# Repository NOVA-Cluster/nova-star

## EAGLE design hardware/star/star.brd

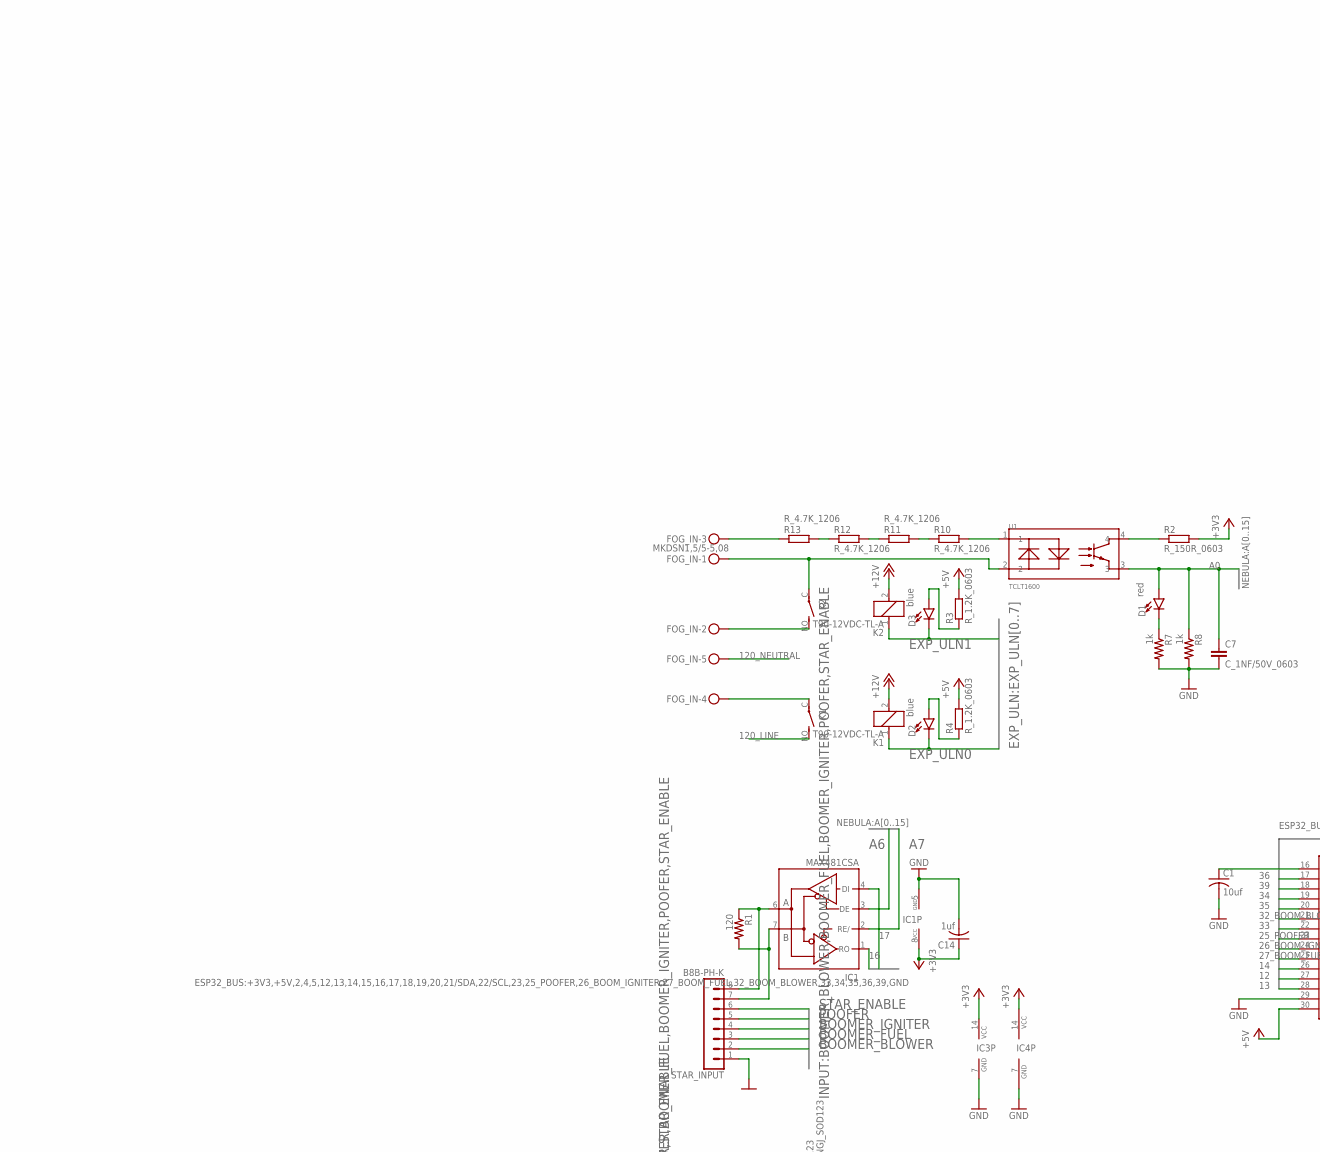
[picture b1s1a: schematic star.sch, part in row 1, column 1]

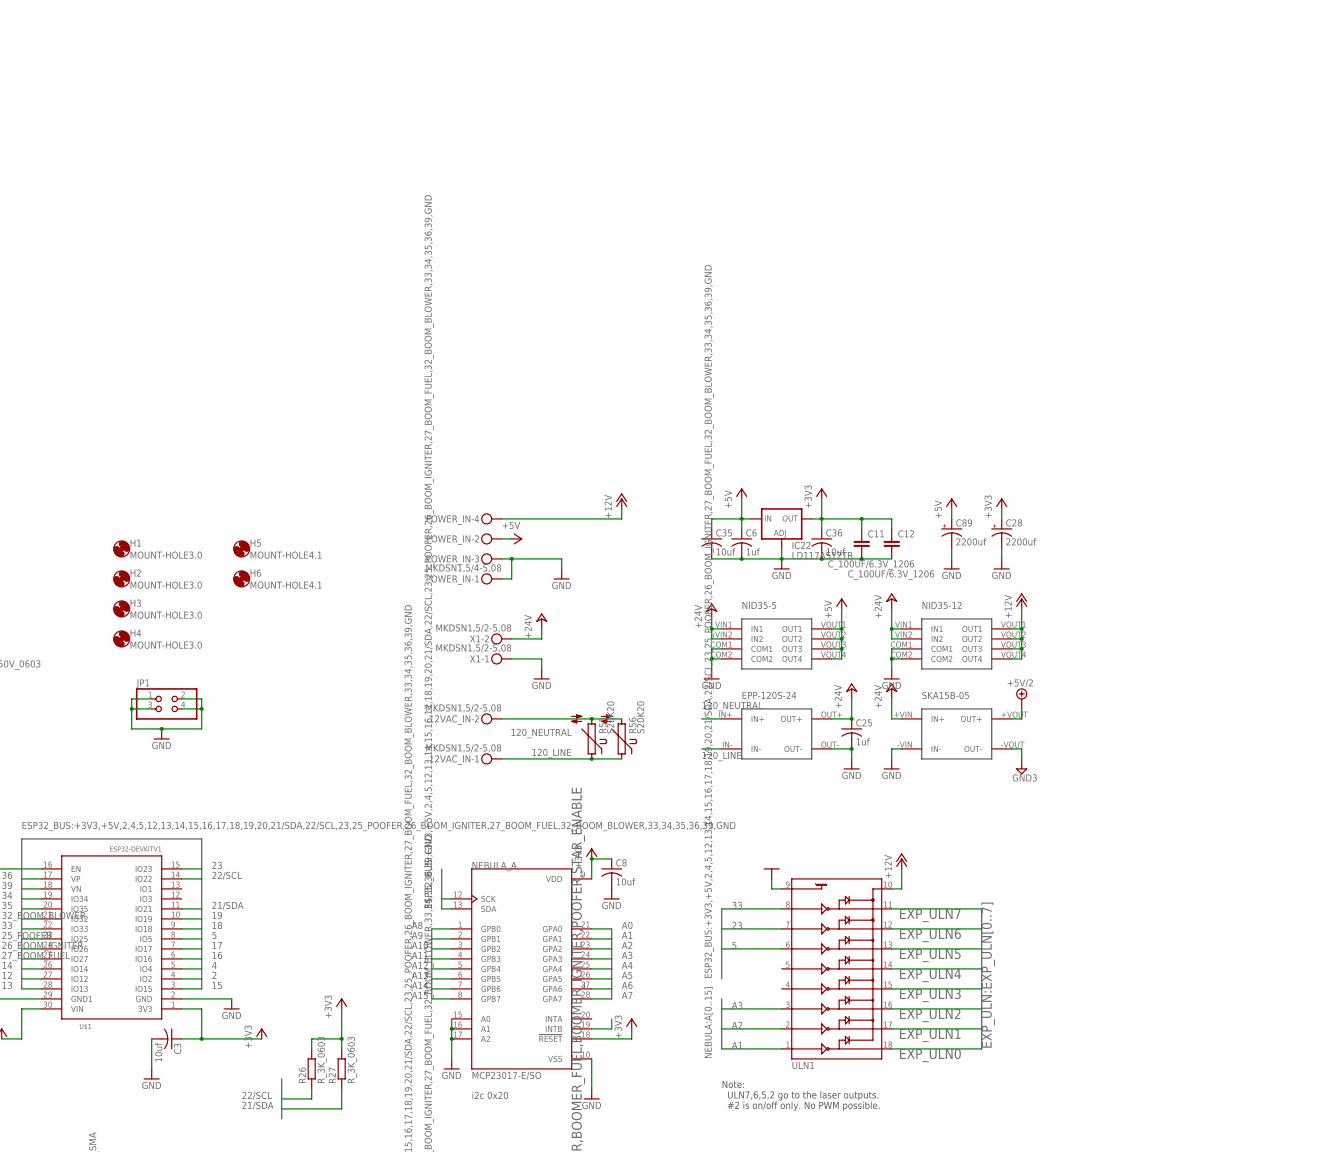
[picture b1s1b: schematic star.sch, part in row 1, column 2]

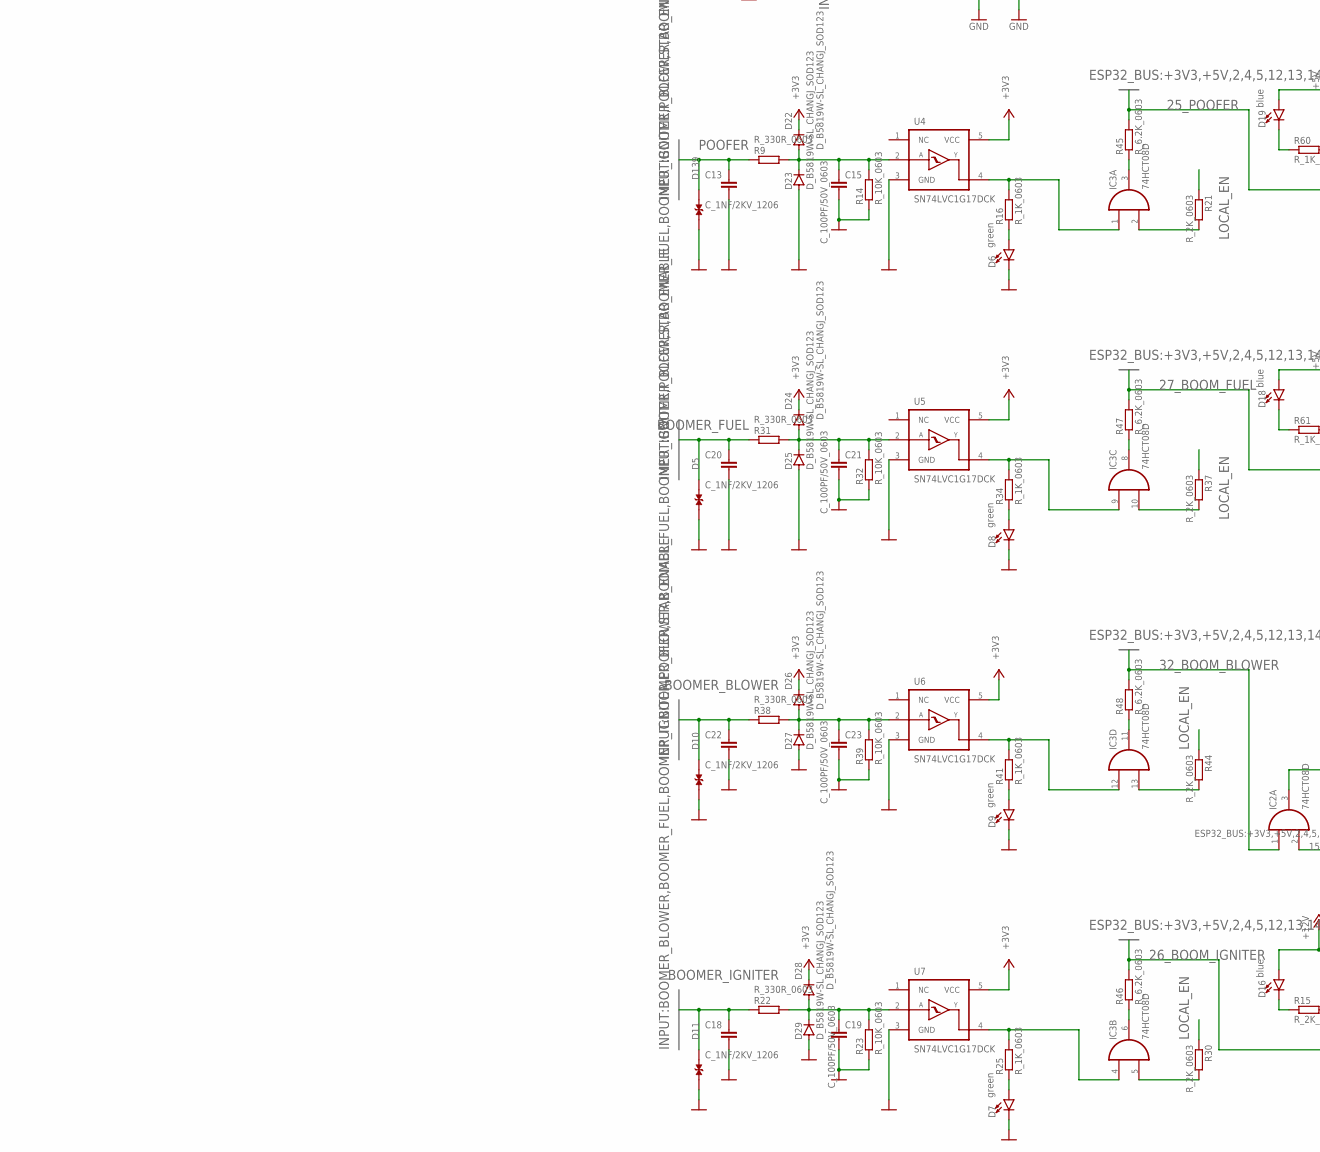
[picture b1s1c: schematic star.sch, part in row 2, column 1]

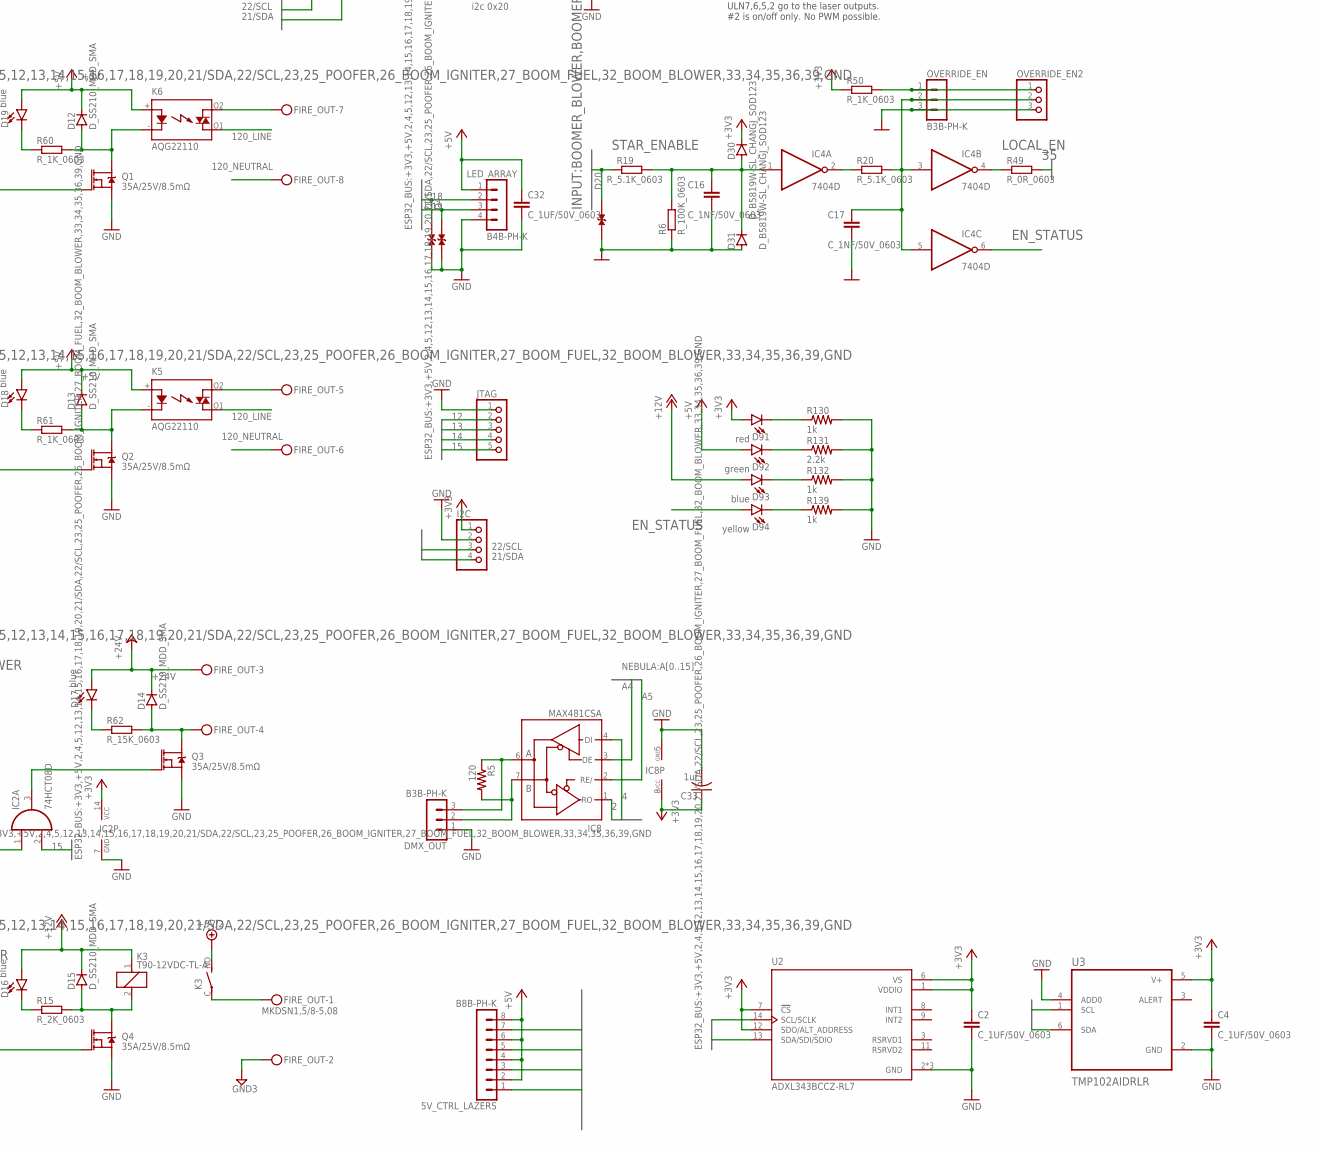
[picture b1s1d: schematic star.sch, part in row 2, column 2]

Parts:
5V_CTRL_LAZERS: B8B-PH-K
12VAC_IN: MKDSN1,5/2-5,08
C1, C3, C8, C35, C36: 10uf; C0603; LCSC_PART C19702
C2, C4, C32: C_1UF/50V_0603; C0603
C6, C14, C25, C33: 1uf; C0805; LCSC_PART C15849
C7, C16, C17: C_1NF/50V_0603; C0603
C11, C12: C_100UF/6.3V_1206; C1206
C13, C18, C20, C22: C_1NF/2KV_1206; C1206
C15, C19, C21, C23: C_100PF/50V_0603; C0603
C28, C89: 2200uf; E5-13
D1, D91: red; LED-0603; JLC_ROTATION 180
D2, D3, D16, D17, D18, D19, D93: blue; LED-0603; JLC_ROTATION 180
D4, D5, D10, D11, D20, D21, D139: SMBJ8.0CA; DIOM4336X265N; LCSC_PART C78757
D6, D7, D8, D9, D92: green; LED-0603; JLC_ROTATION 180
D12, D13, D14, D15: D_SS210_MDD_SMA; DO-214AC
D22, D23, D24, D25, D26, D27, D28, D29, D30, D31: D_B5819W-SL_CHANGJ_SOD123; SOD123
D94: yellow; LED-0603; JLC_ROTATION 180
DMX_OUT: B3B-PH-K
EPP-120S-24: EPP-120S; EPS-25
FIRE_OUT: MKDSN1,5/8-5,08
FOG_IN: MKDSN1,5/5-5,08
H1, H2, H3, H4: MOUNT-HOLE3.0; 3,0
H5, H6: MOUNT-HOLE4.1; 4,1
I2C: PINHD-1X4; 1X04
IC1, IC8: MAX481CSA; SO08; LCSC_PART C8963
IC2, IC3: 74HCT08D; SO14; LCSC_PART C5593
IC4: 7404D; SO14; LCSC_PART C5590
IC22: LD117AS12TR; SOT223; LCSC_PART C347222
JP1: PINHD-2X2; 2X02
JTAG: PINHD-1X5; 1X05
K1, K2, K3: T90-12VDC-TL-A; JT1A-PCB
K5, K6: AQG22110; AQG
LED_ARRAY: B4B-PH-K
NEBULA_A: MCP23017-E/SO; SOIC127P1030X265-28N; LCSC_PART C629440
NID35-5, NID35-12: NID35
OVERRIDE_EN: B3B-PH-K
OVERRIDE_EN2: PINHD-1X3; 1X03
POWER_IN: MKDSN1,5/4-5,08
Q1, Q2, Q3, Q4: 35A/25V/8.5mΩ; DPAK; LCSC_PART C2995335
R1, R5: 120; R0603; LCSC_PART C22787
R2: R_150R_0603; R0603
R3, R4: R_1.2K_0603; R0603
R6: R_100K_0603; R0603
R7, R8, R130, R132, R139: 1k; R0603; LCSC_PART C21190
R9, R22, R31, R38: R_330R_0603; R0603
R10, R11, R12, R13: R_4.7K_1206; R1206
R14, R23, R32, R39: R_10K_0603; R0603
R15, R21, R30, R37, R44: R_2K_0603; R0603
R16, R25, R34, R41, R50, R60, R61: R_1K_0603; R0603
R19, R20: R_5.1K_0603; R0603
R26, R27: R_3K_0603; R0603
R45, R46, R47, R48: R_6.2K_0603; R0603
R49: R_0R_0603; R0603
R55, R56: S20K20
R62: R_15K_0603; R0603
R131: 2.2k; R0603; LCSC_PART C4190
SKA15B-05: SKA15B
STAR_INPUT: B8B-PH-K
U1: TCLT1600; SOP254P1015X230-4N; LCSC_PART C553998
U2: ADXL343BCCZ-RL7; PQFN80P300X500X100-14N; LCSC_PART C9667
U3: TMP102AIDRLR; SOT50P160X60-6N
U4, U5, U6, U7: SN74LVC1G17DCK; SC70-5
U$1: ESP32DEVKITV1; ESP32-DEVKITV1
ULN1: ULN2803SOICW; SO18L; LCSC_PART C9683
X1: MKDSN1,5/2-5,08

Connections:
2: IC8.1 (RO), U$1.4 (IO2)
4: IC8.4 (DI), U$1.5 (IO4)
5: U$1.8 (IO5), ULN1.6
12: JTAG.2, U$1.27 (IO12)
13: JTAG.3, U$1.28 (IO13)
14: JTAG.4, U$1.26 (IO14)
15: IC2.2 (I1), JTAG.5, U$1.3 (IO15)
16: IC1.1 (RO), U$1.6 (IO16)
17: IC1.4 (DI), U$1.7 (IO17)
18: D21.2, LED_ARRAY.2, U$1.9 (IO18)
19: D4.2, LED_ARRAY.3, U$1.10 (IO19)
21/SDA: I2C.4, NEBULA_A.13 (SDA), R27.1, U2.13 (SDA/SDI/SDIO), U3.6 (SDA), U$1.11 (IO21)
22/SCL: I2C.3, NEBULA_A.12 (SCK), R26.1, U2.14 (SCL/SCLK), U3.1 (SCL), U$1.14 (IO22)
23: U$1.15 (IO23), ULN1.7
25_POOFER: Q1.1 (G), R45.2, U$1.23 (IO25)
26_BOOM_IGNITER: Q4.1 (G), R46.2, U$1.24 (IO26)
27_BOOM_FUEL: Q2.1 (G), R47.2, U$1.25 (IO27)
32_BOOM_BLOWER: IC2.1 (I0), R48.2, U$1.21 (IO32)
33: U$1.22 (IO33), ULN1.8
34: NEBULA_A.19 (INTB), U$1.19 (IO34)
35: R49.2, U$1.20 (IO35)
36: U$1.17 (VP)
39: U$1.18 (VN)
120_LINE: 12VAC_IN.1, EPP-120S-24.IN-, K1.NO (S), K5.O1 (DS2), K6.O1 (DS2), R55.1, R56.1
120_NEUTRAL: 12VAC_IN.2, EPP-120S-24.IN+, FIRE_OUT.6, FIRE_OUT.8, FOG_IN.5, R55.2, R56.2
+3V3: C2.1, C3.1, C4.1, C8.1, C11.1, C12.1, C14.1, C28.+, C33.1, C36.1, D22.C, D24.C, D26.C, D28.C, D30.C, D91.A, I2C.1, IC1.8 (VCC), IC2.14 (VCC), IC3.14 (VCC), IC4.14 (VCC), IC8.8 (VCC), IC22.4 (OUT), NEBULA_A.9 (VDD), NEBULA_A.18 (!RESET), R2.2, R26.2, R27.2, R50.1, U2.1 (VDDIO), U2.6 (VS), U2.7 (!CS), U2.12 (SDO/ALT_ADDRESS), U3.5 (V+), U4.5 (VCC), U5.5 (VCC), U6.5 (VCC), U7.5 (VCC), U$1.1 (3V3)
+5V: 5V_CTRL_LAZERS.2, 5V_CTRL_LAZERS.4, 5V_CTRL_LAZERS.6, 5V_CTRL_LAZERS.8, C6.1, C32.1, C35.1, C89.+, D12.C, D13.C, D18.A, D19.A, D92.A, IC22.3 (IN), K5.+ (A), K6.+ (A), LED_ARRAY.1, NID35-5.VOUT1 (OUT1), NID35-5.VOUT2 (OUT2), NID35-5.VOUT3 (OUT3), NID35-5.VOUT4 (OUT4), POWER_IN.2, R3.2, R4.2, U$1.30 (VIN)
+5V/2: K3.NO (S), SKA15B-05.+VOUT (OUT+)
+12V: D15.C, D16.A, D93.A, K1.2, K2.2, K3.1, NID35-12.VOUT1 (OUT1), NID35-12.VOUT2 (OUT2), NID35-12.VOUT3 (OUT3), NID35-12.VOUT4 (OUT4), POWER_IN.4, ULN1.10
+24V: C25.1, D14.C, D17.A, EPP-120S-24.OUT+, FIRE_OUT.3, NID35-5.VIN1 (IN1), NID35-5.VIN2 (IN2), NID35-12.VIN1 (IN1), NID35-12.VIN2 (IN2), SKA15B-05.+VIN (IN+), X1.2
A0: C7.1, D1.A, NEBULA_A.21 (GPA0), R8.1, U1.3
A1: NEBULA_A.22 (GPA1), ULN1.1
A2: NEBULA_A.23 (GPA2), ULN1.2
A3: NEBULA_A.24 (GPA3), ULN1.3
A4: IC8.3 (DE), NEBULA_A.25 (GPA4)
A5: IC8.2 (RE/), NEBULA_A.26 (GPA5)
A6: IC1.3 (DE), NEBULA_A.27 (GPA6)
A7: IC1.2 (RE/), NEBULA_A.28 (GPA7)
A8: NEBULA_A.1 (GPB0)
A9: NEBULA_A.2 (GPB1)
A10: NEBULA_A.3 (GPB2)
A11: NEBULA_A.4 (GPB3)
A12: NEBULA_A.5 (GPB4)
A13: NEBULA_A.6 (GPB5)
A14: NEBULA_A.7 (GPB6)
A15: NEBULA_A.8 (GPB7)
BOOMER_BLOWER: C22.1, D10.2, R38.1, STAR_INPUT.2
BOOMER_FUEL: C20.1, D5.2, R31.1, STAR_INPUT.3
BOOMER_IGNITER: C18.1, D11.2, R22.1, STAR_INPUT.4
EN_STATUS: D94.A, IC4.6 (O)
EXP_ULN0: D2.C, K1.1, ULN1.18
EXP_ULN1: D3.C, K2.1, ULN1.17
EXP_ULN2: 5V_CTRL_LAZERS.7, ULN1.16
EXP_ULN3: ULN1.15
EXP_ULN4: ULN1.14
EXP_ULN5: 5V_CTRL_LAZERS.5, ULN1.13
EXP_ULN6: 5V_CTRL_LAZERS.3, ULN1.12
EXP_ULN7: 5V_CTRL_LAZERS.1, ULN1.11
GND: C1.2, C2.2, C3.2, C4.2, C6.2, C7.2, C8.2, C11.2, C12.2, C13.2, C14.2, C15.2, C16.2, C17.2, C18.2, C19.2, C20.2, C21.2, C22.2, C23.2, C25.2, C28.-, C32.2, C33.2, C35.2, C36.2, C89.-, D4.1, D5.1, D6.C, D7.C, D8.C, D9.C, D10.1, D11.1, D20.1, D21.1, D23.A, D25.A, D27.A, D29.A, D31.A, D139.1, DMX_OUT.1, EPP-120S-24.OUT-, I2C.2, IC1.5 (GND), IC2.7 (GND), IC3.7 (GND), IC4.7 (GND), IC8.5 (GND), IC22.1 (ADJ), JP1.1, JP1.2, JP1.3, JP1.4, JTAG.1, LED_ARRAY.4, NEBULA_A.10 (VSS), NEBULA_A.15 (A0), NEBULA_A.16 (A1), NEBULA_A.17 (A2), NID35-5.COM1, NID35-5.COM2, NID35-12.COM1, NID35-12.COM2, OVERRIDE_EN.3, OVERRIDE_EN2.3, POWER_IN.1, POWER_IN.3, Q1.3 (S), Q2.3 (S), Q3.3 (S), Q4.3 (S), R6.1, R7.2, R8.2, R14.1, R23.1, R32.1, R39.1, R130.2, R131.2, R132.2, R139.2, SKA15B-05.-VIN (IN-), STAR_INPUT.1, U2.2 (GND), U2.4 (GND), U2.5 (GND), U3.2 (GND), U3.4 (ADD0), U4.3 (GND), U5.3 (GND), U6.3 (GND), U7.3 (GND), U$1.2 (GND), U$1.29 (GND1), ULN1.9, X1.1
GND3: FIRE_OUT.2, SKA15B-05.-VOUT (OUT-)
LOCAL_EN: IC4.4 (O), R21.1, R30.1, R37.1, R44.1, R49.1
unnamed: C1.1, U$1.16 (EN)
unnamed: R2.1, U1.4
unnamed: D2.A, R4.1
unnamed: D3.A, R3.1
unnamed: DMX_OUT.2, IC8.7 (B), R5.2
unnamed: DMX_OUT.3, IC8.6 (A), R5.1
unnamed: FOG_IN.3, R13.1
unnamed: R12.1, R13.2
unnamed: R11.1, R12.2
unnamed: R10.1, R11.2
unnamed: R10.2, U1.1
unnamed: D1.C, R7.1
unnamed: FOG_IN.2, K2.NO (S)
unnamed: FOG_IN.4, K1.C
unnamed: FOG_IN.1, K2.C, U1.2
unnamed: IC3.1 (I0), R16.2, U4.4 (Y)
unnamed: C15.1, D22.A, D23.C, R9.2, R14.2, U4.2 (A)
unnamed: D6.A, R16.1
unnamed: IC4.2 (O), R20.1
unnamed: C17.1, IC4.3 (I), IC4.5 (I), OVERRIDE_EN.2, OVERRIDE_EN2.2, R20.2
unnamed: C16.1, D30.A, D31.C, IC4.1 (I), R6.2, R19.2
unnamed: IC3.2 (I1), R21.2
unnamed: C19.1, D28.A, D29.C, R22.2, R23.2, U7.2 (A)
unnamed: IC3.4 (I0), R25.2, U7.4 (Y)
unnamed: D7.A, R25.1
unnamed: IC3.5 (I1), R30.2
unnamed: C21.1, D24.A, D25.C, R31.2, R32.2, U5.2 (A)
unnamed: IC3.9 (I0), R34.2, U5.4 (Y)
unnamed: D8.A, R34.1
unnamed: IC3.10 (I1), R37.2
unnamed: C23.1, D26.A, D27.C, R38.2, R39.2, U6.2 (A)
unnamed: IC3.12 (I0), R41.2, U6.4 (Y)
unnamed: D9.A, R41.1
unnamed: IC3.13 (I1), R44.2
unnamed: IC3.3 (O), R45.1
unnamed: IC3.6 (O), R46.1
unnamed: IC3.8 (O), R47.1
unnamed: IC3.11 (O), R48.1
unnamed: D13.A, K5.- (K), Q2.4 (D), R61.2
unnamed: FIRE_OUT.7, K6.O2 (DS1)
unnamed: D12.A, K6.- (K), Q1.4 (D), R60.2
unnamed: FIRE_OUT.5, K5.O2 (DS1)
unnamed: D14.A, FIRE_OUT.4, Q3.4 (D), R62.2
unnamed: D15.A, K3.2, Q4.4 (D), R15.2
unnamed: FIRE_OUT.1, K3.C
unnamed: D16.C, R15.1
unnamed: D17.C, R62.1
unnamed: D18.C, R61.1
unnamed: D19.C, R60.1
unnamed: OVERRIDE_EN.1, OVERRIDE_EN2.1, R50.2
unnamed: IC2.3 (O), Q3.1 (G)
unnamed: IC1.7 (B), R1.2, STAR_INPUT.7
unnamed: IC1.6 (A), R1.1, STAR_INPUT.8
unnamed: D91.C, R130.1
unnamed: D92.C, R131.1
unnamed: D93.C, R132.1
unnamed: D94.C, R139.1
POOFER: C13.1, D139.2, R9.1, STAR_INPUT.5
STAR_ENABLE: D20.2, R19.1, STAR_INPUT.6

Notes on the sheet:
i2c 0x20
Note: ULN7,6,5,2 go to the laser outputs. #2 is on/off only. No PWM possible.

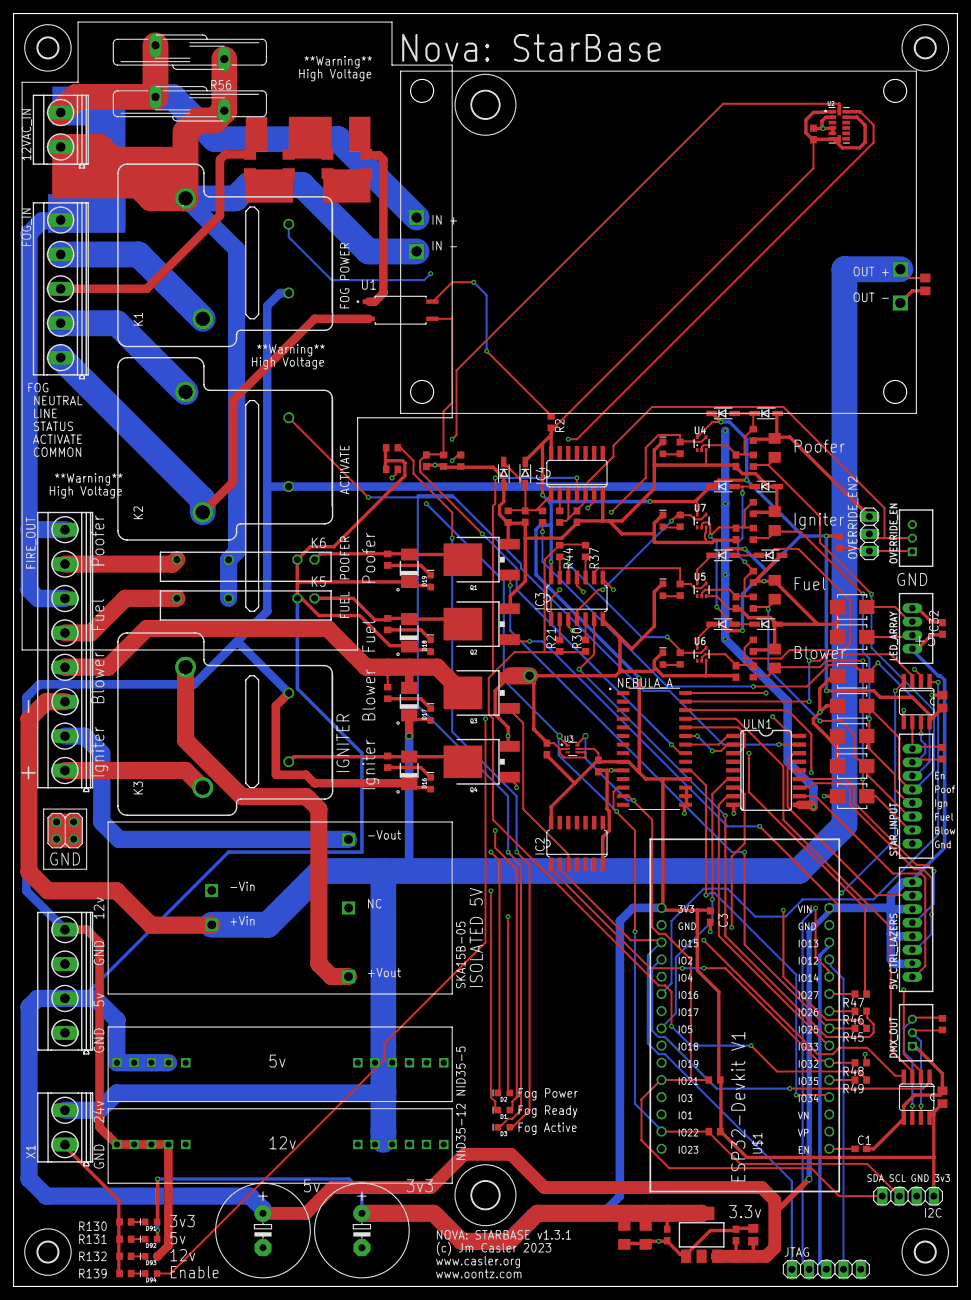
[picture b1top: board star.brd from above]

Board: 4 copper layers, 139.4 x 187.9 mm, 160 parts (0 on the bottom side), 108 nets.

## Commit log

2022-12-23 Initial check in. Populated with a copy/paste of the core pcb files
2023-01-04 Progress
2023-01-14 more progress
2023-01-14 manual traces
2023-01-14 critical traces routed
2023-01-14 v01 - complete and ordered
2023-02-10 Added buckboost
2023-02-16 Add TVS diodes
2023-02-17 I think it's good?
2023-02-17 Manual Routing Complete for v2
2023-02-18 Swapped 1.5A fuse with 5A fuse
2023-02-18 Updated labels
2023-02-22 Added switching 5v regulator
2023-02-24 Block diagram of power system for starbase
2023-02-24 Lots of updates
2023-02-24 update few traces
2023-02-24 Manual routing complete
2023-02-24 starbase v02
2023-03-11 swap to schmitt trigger
2023-03-11 change hole size
2023-03-12 Starbase 1.3.0 Final
2023-03-12 v1.3.0 final
2023-04-09 Initial code for starbase
2023-04-09 StarBase 1.3.1
2023-04-09 set random fog machine operation
2023-04-09 Firmware is at MVP and will control the fog machine.
2023-04-09 moved pins of NID35 down 0.05in
2023-04-10 Set analog duty of blower
2023-04-10 change folders
2023-04-10 something just happened
2023-04-11 Update silkscreen of i2c output
2023-04-15 Cleanup main.cpp
2023-04-20 update fog machine timings
2023-06-14 Able to set DMX colors for two RBG fixtures
2023-06-14 Finished the MVP of the dmx512 firmware and the integration with FastLED.
2023-07-05 Add: DMX Thread, Protos, NovaIO and NovaNet
2023-07-07 add esp32 backtrace decoder
2023-07-07 initial receiver functions
2023-07-13 Removed
2023-07-13 Moved DMX to a thread
2023-07-14 cleanup
2023-07-16 NovaNet to DMX512 works!
2023-07-16 update comment
2023-07-16 update for performance
2023-07-16 delete
2023-07-23 Updated .gitignore
2023-07-27 Update star with control of the fog machine
2023-07-27 update task priorities
2023-07-27 back to reading the io
2023-07-27 write out the received frame rate

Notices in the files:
parts and their libraries:
SparkFun-LED: Licensing: Creative Commons ShareAlike 4.0 International - https://creativecommons.org/licenses/by-sa/4.0
con-jst-ph: Copyright (C) 2016, Bob Starr
